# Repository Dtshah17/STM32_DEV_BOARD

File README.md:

#﻿# STM32 DEV BOARD

## Table of Contents
 
- [Overview](#overview)
- [Features](#features)
- [Notes](#notes)

## Overview

The STM32 Dev Board is a simple PoC design utilising the STM32F070C6 MCU

## Features 

The devboard features the following:

- USB-C Power and Program Input
- 5V to 3.3V Voltage Regulation 
- 4MB QSPI FLASH Memory 
- External 8MHz Crystal 
- MOSFET Driven BOOT and Reset Switch 
- USART Interface
- SWD Debugging Interface
- Host I2C Protocal Interface
- Status LEDs

## Notes 
 - 1/3/26 : Initial Commit to git
 - 3/3/26 : Minor Repo Updates
 - 10/3/26 : Repo Declared Unusable 
 - 11/3/26 : Files updated locally 
 
 - 15/3/26 : Reinit to git files uploaded
 - 15/3/26 : PCB Schematic broken, netlist items incorrectly assigned 
 - 15/3/26 : Issues arisen due to version change and file type mishandling
 - 15/3/26 : WIP Redesign of PCB
 - 15/3/26 : Temporarily Removed PCB file from Main

## Upcoming 
 - Embed sensors including BME208 Barometric Pressure Sensor
 - Design motion suite HAT for board including gyroscope
 - Program over Air and PPoE HAT

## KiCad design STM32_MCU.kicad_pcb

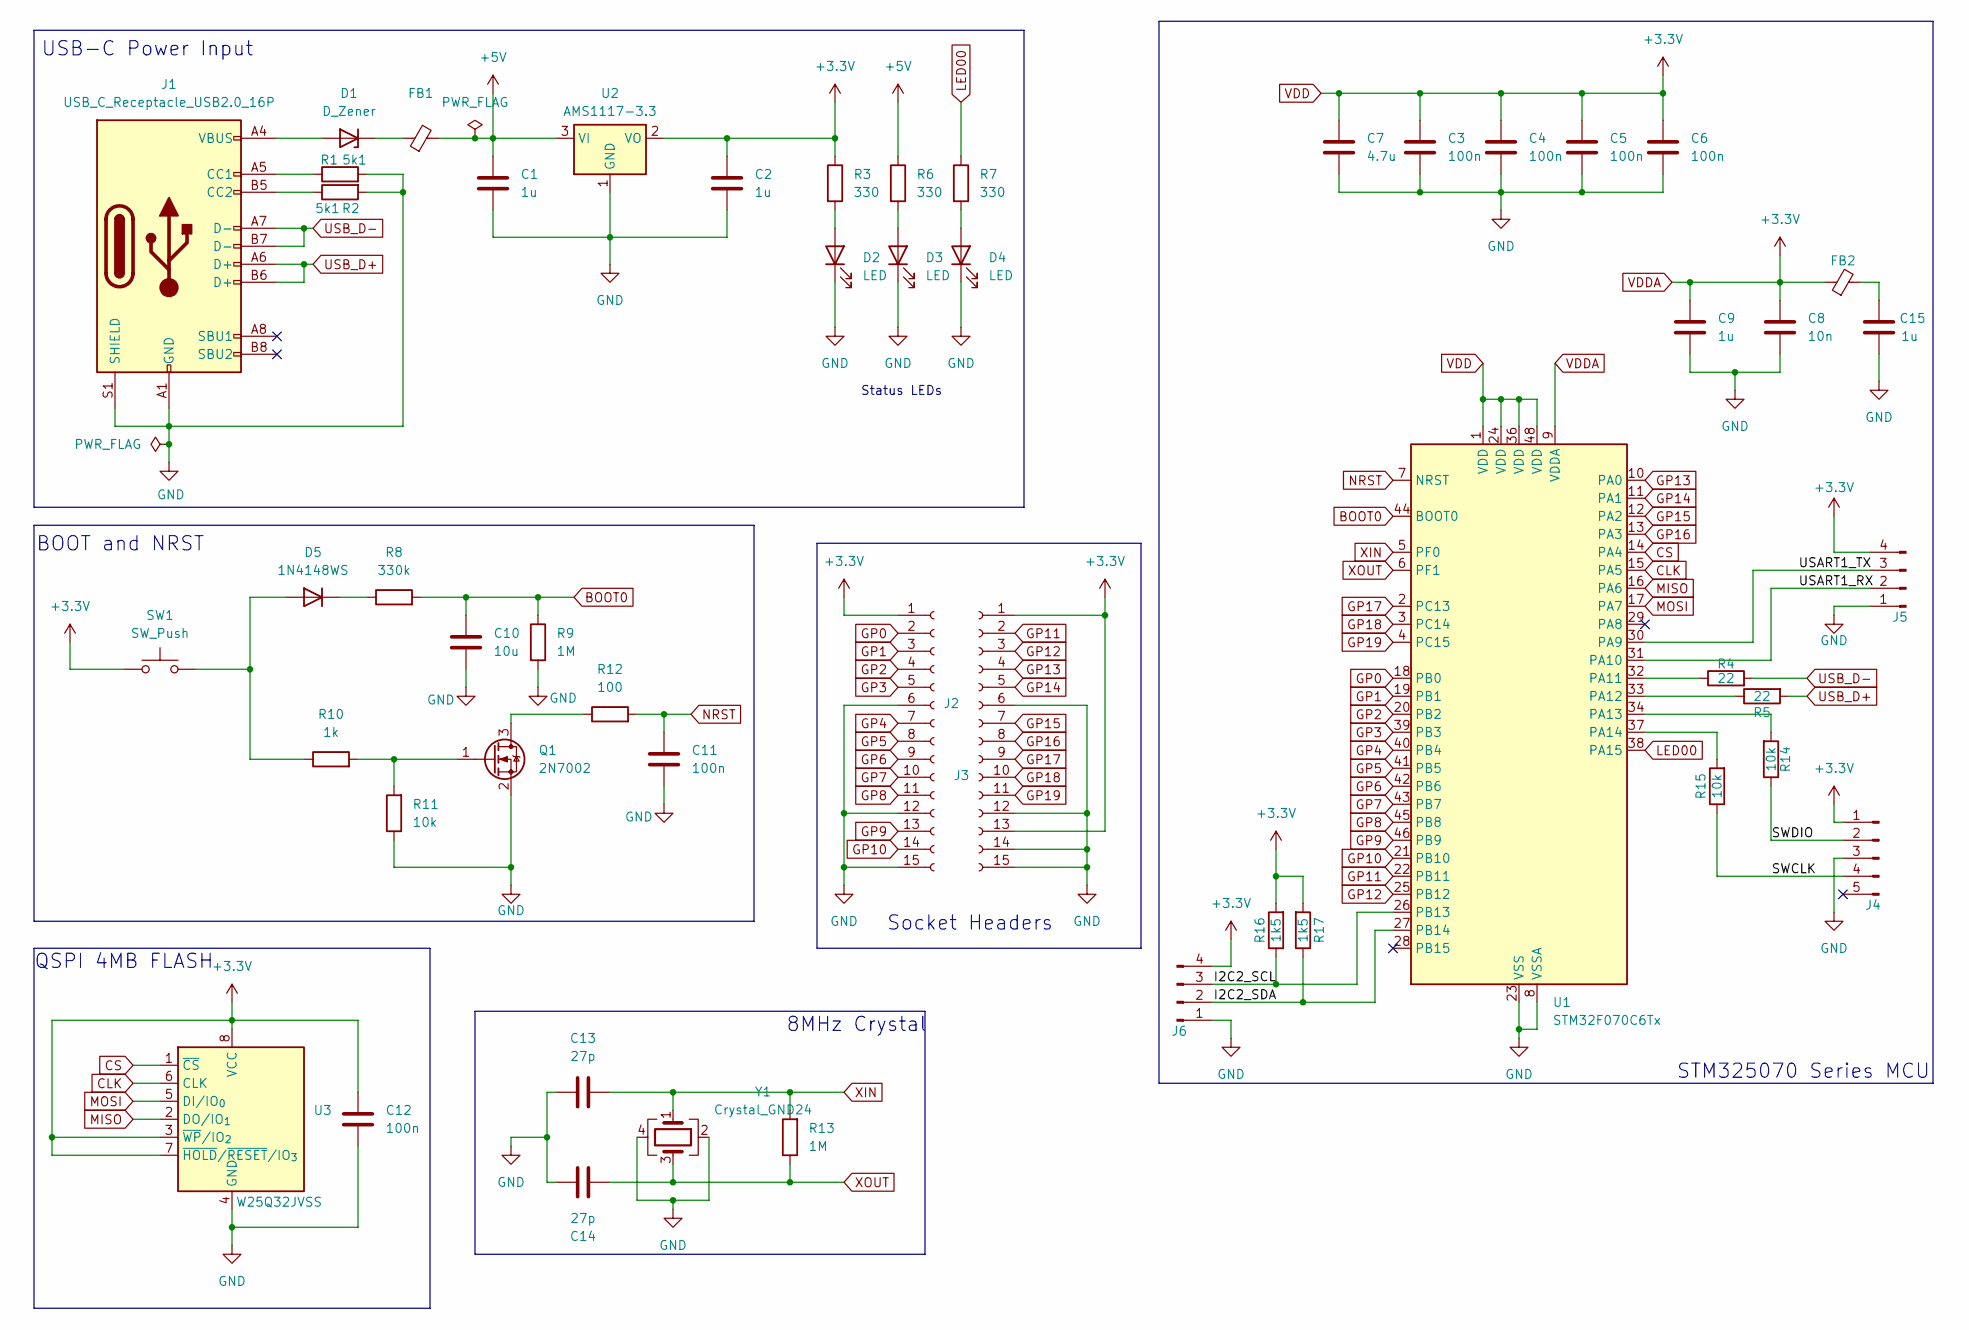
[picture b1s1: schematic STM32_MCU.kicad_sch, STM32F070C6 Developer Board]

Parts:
C1, C2, C9, C15: 1u; C_0402_1005Metric
C3, C4, C5, C6, C11, C12: 100n; C_0402_1005Metric
C7: 4.7u; C_0603_1608Metric
C8: 10n; C_0603_1608Metric
C10: 10u; C_0603_1608Metric
C13, C14: 27p; C_0402_1005Metric
D1: D_Zener; D_SOD-323
D2, D3, D4: LED; LED_0603_1608Metric
D5: 1N4148WS; D_SOD-323
FB1, FB2: FerriteBead_Small; L_0402_1005Metric
J1: USB_C_Receptacle_USB2.0_16P; USB_C_Receptacle_GCT_USB4105-xx-A_16P_TopMnt_Horizontal
J2, J3: Conn_01x15_Socket; PinHeader_1x15_P2.54mm_Vertical
J4: Conn_01x05_Pin; PinHeader_1x05_P2.54mm_Vertical
J5, J6: Conn_01x04_Pin; PinHeader_1x04_P2.54mm_Vertical
Q1: 2N7002; SOT-23
R1, R2: 5k1; R_0402_1005Metric
R3, R6, R7: 330; R_0402_1005Metric
R4, R5: 22; R_0402_1005Metric
R8: 330k; R_0402_1005Metric
R9, R13: 1M; R_0402_1005Metric
R10: 1k; R_0402_1005Metric
R11, R14, R15: 10k; R_0402_1005Metric
R12: 100; R_0402_1005Metric
R16, R17: 1k5; R_0402_1005Metric
SW1: SW_Push; SW_PUSH_6mm_H4.3mm
U1: STM32F070C6Tx; LQFP-48_7x7mm_P0.5mm
U2: AMS1117-3.3; SOT-223-3_TabPin2
U3: W25Q32JVSS; SOIC-8_5.3x5.3mm_P1.27mm
Y1: Crystal_GND24; Crystal_SMD_Abracon_ABM8G-4Pin_3.2x2.5mm

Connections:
+5V: C1.1, FB1.2, R6.1, U2.3 (VI)
/I2C2_SCL: J6.3, R16.1, U1.26 (PB13)
/I2C2_SDA: J6.2, R17.1, U1.27 (PB14)
/SWCLK: J4.4, R15.1
/SWDIO: J4.2, R14.1
/USART1_RX: J5.2, U1.31 (PA10)
/USART1_TX: J5.3, U1.30 (PA9)
BOOT0: C10.1, R8.2, R9.1, U1.44 (BOOT0)
CLK: U1.15 (PA5), U3.6 (CLK)
CS: U1.14 (PA4), U3.1 (~CS)
GND: C1.2, C2.2, C3.2, C4.2, C5.2, C6.2, C7.2, C8.2, C9.2, C10.2, C11.2, C12.2, C13.1, C14.1, C15.2, D2.1 (K), D3.1 (K), D4.1 (K), J1.A1 (GND), J1.A12 (GND), J1.B1 (GND), J1.B12 (GND), J1.S1 (SHIELD), J2.6, J2.12, J2.15, J3.6, J3.12, J3.14, J3.15, J4.3, J5.1, J6.1, Q1.2 (S), R1.2, R2.2, R9.2, R11.1, U1.8 (VSSA), U1.23 (VSS), U1.35 (VSS), U1.47 (VSS), U2.1 (GND), U3.4 (GND), Y1.2, Y1.4
GP0: J2.2, U1.18 (PB0)
GP1: J2.3, U1.19 (PB1)
GP2: J2.4, U1.20 (PB2)
GP3: J2.5, U1.39 (PB3)
GP4: J2.7, U1.40 (PB4)
GP5: J2.8, U1.41 (PB5)
GP6: J2.9, U1.42 (PB6)
GP7: J2.10, U1.43 (PB7)
GP8: J2.11, U1.45 (PB8)
GP9: J2.13, U1.46 (PB9)
GP10: J2.14, U1.21 (PB10)
GP11: J3.2, U1.22 (PB11)
GP12: J3.3, U1.25 (PB12)
GP13: J3.4, U1.10 (PA0)
GP14: J3.5, U1.11 (PA1)
GP15: J3.7, U1.12 (PA2)
GP16: J3.8, U1.13 (PA3)
GP17: J3.9, U1.2 (PC13)
GP18: J3.10, U1.3 (PC14)
GP19: J3.11, U1.4 (PC15)
LED00: R7.1, U1.38 (PA15)
MISO: U1.16 (PA6), U3.2 (DO/IO_{1})
MOSI: U1.17 (PA7), U3.5 (DI/IO_{0})
NRST: C11.1, R12.2, U1.7 (NRST)
unnamed: C15.1, FB2.2
unnamed: D1.2 (A), J1.A4 (VBUS), J1.A9 (VBUS), J1.B4 (VBUS), J1.B9 (VBUS)
unnamed: D1.1 (K), FB1.1
unnamed: D2.2 (A), R3.2
unnamed: D3.2 (A), R6.2
unnamed: D4.2 (A), R7.2
unnamed: D5.2 (A), R10.1, SW1.2
unnamed: D5.1 (K), R8.1
unnamed: J1.A5 (CC1), R1.1
unnamed: J1.B5 (CC2), R2.1
unnamed: Q1.3 (D), R12.1
unnamed: Q1.1 (G), R10.2, R11.2
unnamed: R4.1, U1.32 (PA11)
unnamed: R5.1, U1.33 (PA12)
unnamed: R14.2, U1.34 (PA13)
unnamed: R15.2, U1.37 (PA14)
USB_D+: J1.A6 (D+), J1.B6 (D+), R5.2
USB_D-: J1.A7 (D-), J1.B7 (D-), R4.2
VDD: C2.1, C3.1, C4.1, C5.1, C6.1, C7.1, C8.1, C9.1, C12.1, FB2.1, J2.1, J3.1, J3.13, J4.1, J5.4, J6.4, R3.1, R16.2, R17.2, SW1.1, U1.1 (VDD), U1.9 (VDDA), U1.24 (VDD), U1.36 (VDD), U1.48 (VDD), U2.2 (VO), U3.3 (~WP/IO_{2}), U3.7 (~HOLD/~RESET/IO_{3}), U3.8 (VCC)
XIN: C13.2, R13.2, U1.5 (PF0), Y1.1
XOUT: C14.2, R13.1, U1.6 (PF1), Y1.3

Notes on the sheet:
Socket Headers
8MHz Crystal
STM325070 Series MCU
Status LEDs
QSPI 4MB FLASH
BOOT and NRST
USB-C Power Input

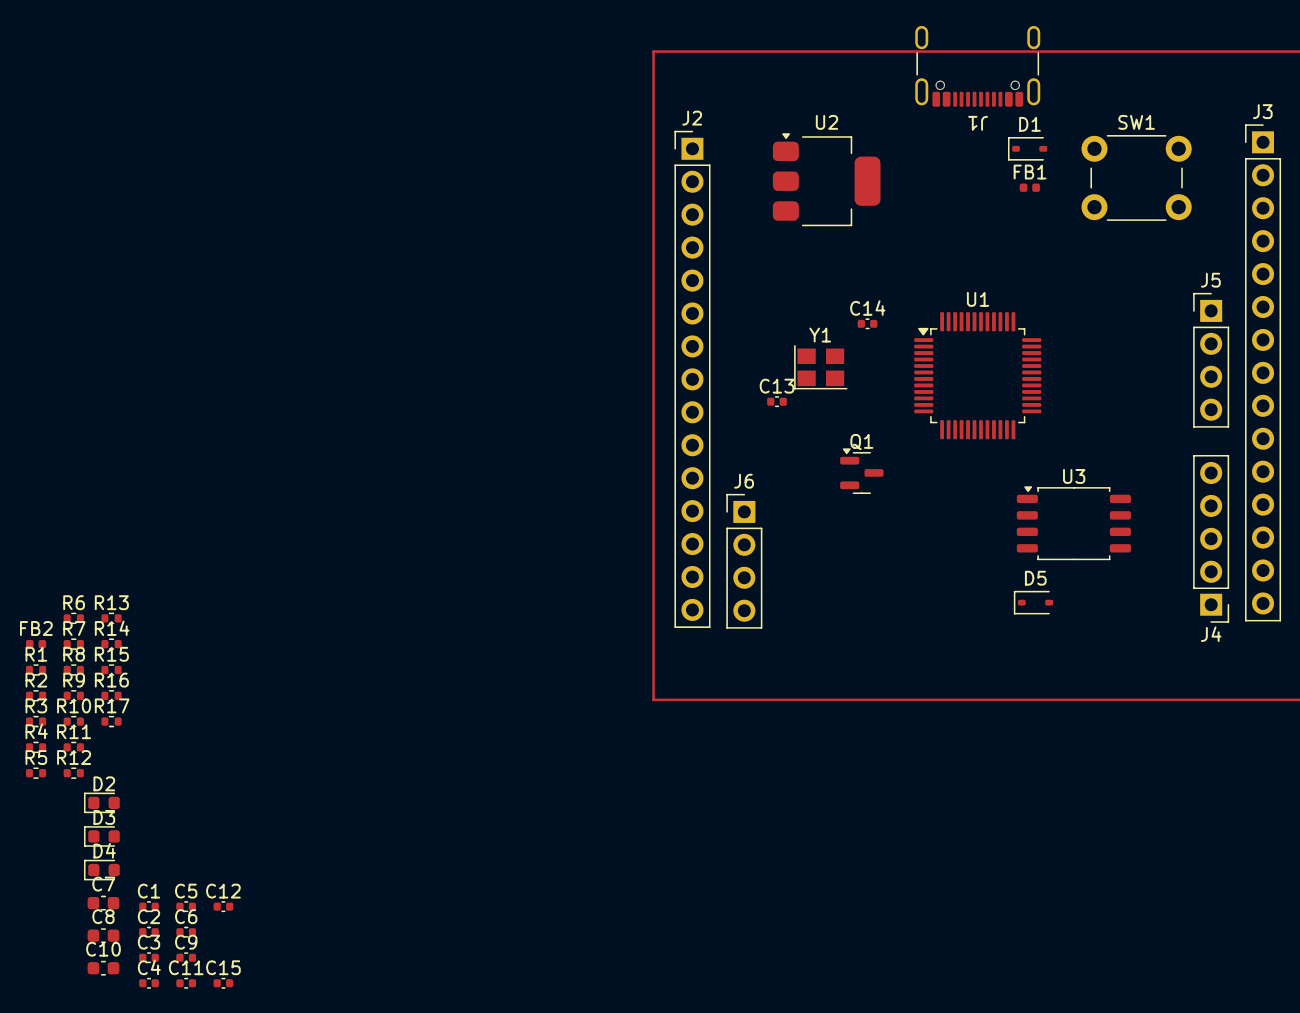
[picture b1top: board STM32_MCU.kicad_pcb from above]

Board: 2 copper layers, 51 parts (0 on the bottom side), 56 nets.

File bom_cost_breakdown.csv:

Reference,Description,Value,Package,Qty,Unit Price (USD),Line Total (USD),Supplier,Notes
C1+C2+C9+C15,Capacitor,1u,0402,4,0.01,0.04,LCSC,Generic MLCC
C3+C4+C5+C6+C11+C12,Capacitor,100n,0402,6,0.01,0.06,LCSC,Generic MLCC
C7,Capacitor,4.7u,0603,1,0.02,0.02,LCSC,Generic MLCC
C8,Capacitor,10n,0603,1,0.02,0.02,LCSC,Generic MLCC
C10,Capacitor,10u,0603,1,0.02,0.02,LCSC,Generic MLCC
C13+C14,Capacitor,27p,0402,2,0.01,0.02,LCSC,Crystal load caps
D1,Zener Diode,D_Zener,SOD-323,1,0.03,0.03,LCSC,Generic zener
D2+D3+D4,LED,,0603,3,0.05,0.15,LCSC,Generic SMD LED
D5,Diode,1N4148WS,SOD-323,1,0.02,0.02,LCSC,Vishay 1N4148WS
FB1+FB2,Ferrite Bead,FerriteBead_Small,0402,2,0.02,0.04,LCSC,Generic ferrite bead
J1,USB-C Receptacle 16P,USB_C_Receptacle_USB2.0_16P,GCT USB4105,1,0.55,0.55,LCSC,GCT USB4105-GF-A
J2+J3,Pin Socket 1x15,Conn_01x15_Socket,2.54mm THT,2,0.25,0.50,LCSC,1x15 2.54mm socket
J4,Pin Header 1x5,Conn_01x05_Pin,2.54mm THT,1,0.08,0.08,LCSC,1x05 2.54mm header
J5+J6,Pin Header 1x4,Conn_01x04_Pin,2.54mm THT,2,0.07,0.14,LCSC,1x04 2.54mm header
Q1,N-Channel MOSFET,2N7002,SOT-23,1,0.03,0.03,LCSC,OnSemi 2N7002
R1+R2,Resistor,5k1,0402,2,0.01,0.02,LCSC,CC resistors for USB-C
R3+R6+R7,Resistor,330,0402,3,0.01,0.03,LCSC,LED current limiting
R4+R5,Resistor,22,0402,2,0.01,0.02,LCSC,USB D+/D- series
R8,Resistor,330k,0402,1,0.01,0.01,LCSC,Generic
R9+R13,Resistor,1M,0402,2,0.01,0.02,LCSC,Generic
R10,Resistor,1k,0402,1,0.01,0.01,LCSC,Generic
R11+R14+R15,Resistor,10k,0402,3,0.01,0.03,LCSC,Generic pull-up/down
R12,Resistor,100,0402,1,0.01,0.01,LCSC,Generic
R16+R17,Resistor,1k5,0402,2,0.01,0.02,LCSC,USB pull-up
SW1,Tactile Push Button,SW_Push,6mm THT,1,0.08,0.08,LCSC,6mm THT tactile switch
U1,Microcontroller,STM32F070C6Tx,LQFP-48,1,1.20,1.20,LCSC,STMicro STM32F070C6Tx
U2,LDO Regulator,AMS1117-3.3,SOT-223,1,0.12,0.12,LCSC,AMS AMS1117-3.3
U3,SPI Flash 32Mb,W25Q32JVSS,SOIC-8,1,0.35,0.35,LCSC,Winbond W25Q32JVSS
Y1,Crystal,Crystal_GND24,Abracon ABM8G 3.2x2.5mm,1,0.30,0.30,LCSC,SMD crystal with GND pads
,,,,,,,,
,,,,Total Component Count,58,,,
,,,,Total BOM Cost (USD),,3.94,,Estimated at ~qty 10 from LCSC
,,,,Notes,,,,"Prices are representative estimates based on LCSC/JLCPCB market rates (qty 10). Actual prices vary by quantity, availability, and supplier. PCB fabrication and assembly costs not included."

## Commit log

2026-03-15 Upload Schematic and PCB files
2026-03-15 Uploaded README.md
2026-03-15 Added Files to ignore
2026-03-15 .gitignore revised
2026-03-15 Fix formatting and update README structure
2026-03-15 Added cost breakdown
2026-03-15 Added BOM
2026-03-15 Update README with upcoming features
    Added upcoming features section to README.
2026-03-15 Fix formatting issues in README.md
